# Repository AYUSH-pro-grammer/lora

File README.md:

# Lora

A LoRa board project that I made in order to figure out how radios really work, rather than just reading about them. It was a great way for me to do some PCB design and play around with KiCad, while learning what to do when things don’t go according to plan (which happened quite a bit).

# How its works

This board is a custom designed wireless communication module for long range applications. It is based on the dual-core Raspberry Pi RP2040 microcontroller and SX1262 LoRa transceiver.

- Power & Connectivity. 5V power and data thru USB-C port. An AP2112K-3.3 LDO regulator efficiently steps this down to a stable 3.3V for the system.

- Processing & Memory - The RP2040 is the brain. The RP2040 requires external memory, so it’s coupled with a W25Q16JV SPI Flash chip to store your firmware.

- Long-Range RF The SX1262 provides sub-GHz LoRa wireless communication. The RF path is controlled by a PE4259 RF switch and a Johanson Balun to condition the signal for the antenna.

- Internal Routing: The RP2040 uses its SPI busses to talk to the Flash memory and the SX1262 LoRa chip.

```text
[ USB-C ] ──5V──► [ AP2112K-3.3 LDO ] ──3.3V──┐
                                              ▼
[ W25Q16 Flash ] ◄──SPI── [ RP2040 ] ──SPI──► [ SX1262 LoRa ]
                        (Main Brain)                │
                                                    ▼
                                            [ PE4259 Switch ]
                                                    │
                                                    ▼
                                                [ Antenna ]
                                                    📡

```

# Images:

## 3d

## Schematic

## PCB 

## Components

Total Physical Components: 53
Capacitors: 28
Resistors: 8
Inductors: 3
Crystals/Oscillators: 2
Push Buttons (Cherry MX): 2
Antenna / Pin Headers: 2 (1 Spring Antenna + 1 Pin Header)
Ferrite Beads: 1
RF Baluns: 1
USB-C Connectors: 1
Voltage Regulators (AP2112K): 1
RF Switches (PE4259): 1
Flash Memory (W25Q16JV): 1
SX1262 LoRa IC: 1
RP2040 Microcontroller: 1

## BOM

|  Qty  | Component                                    | Selected Part                 | Supplier  | Link                                                                        | MOQ | Unit Price (USD) | Order Cost (USD) |
| :---: | :------------------------------------------- | :---------------------------- | :-------- | :-------------------------------------------------------------------------- | --: | ---------------: | ---------------: |
|   1   | LoRa Spring Antenna                          | BW915SNX17-5W2                | LCSC      | [Link](https://www.lcsc.com/product-detail/C496556.html)                    |   5 |           $0.165 |            $0.83 |
|   1   | Antenna Pin Header                           | 2.54-1×40P Pin Header         | LCSC      | [Link](https://www.lcsc.com/product-detail/C2337.html)                      |   5 |           $0.159 |            $0.80 |
|   12  | 100 nF Capacitor                             | 100 nF 16 V 0402 X7R          | LCSC      | [Link](https://www.lcsc.com/product-detail/C1525.html)                      | 100 |           $0.005 |            $0.46 |
|   1   | 150 pF Capacitor                             | 150 pF 50 V 0402 X7R          | LCSC      | [Link](https://www.lcsc.com/product-detail/C1527.html)                      | 100 |           $0.004 |            $0.43 |
|   1   | 20 pF Capacitor                              | 20 pF 50 V 0402 C0G           | LCSC      | [Link](https://www.lcsc.com/product-detail/C1554.html)                      | 100 |           $0.007 |            $0.69 |
|   1   | 220 pF Capacitor                             | 220 pF 50 V 0402 X7R          | LCSC      | [Link](https://www.lcsc.com/product-detail/C1530.html)                      | 100 |           $0.003 |            $0.25 |
|   1   | 1.8 pF Capacitor                             | 1.8 pF 50 V 0402 C0G          | LCSC      | [Link](https://www.lcsc.com/product-detail/C1553.html)                      | 100 |           $0.005 |            $0.50 |
|   2   | 15 pF Capacitor                              | 15 pF 50 V 0402 C0G           | LCSC      | [Link](https://www.lcsc.com/product-detail/C1548.html)                      | 100 |           $0.004 |            $0.36 |
|   2   | 12 pF Capacitor                              | 12 pF 50 V 0402 C0G           | LCSC      | [Link](https://www.lcsc.com/product-detail/C1547.html)                      | 100 |           $0.006 |            $0.60 |
|   2   | 1 pF Capacitor                               | 1 pF 50 V 0402 C0G            | LCSC      | [Link](https://www.lcsc.com/product-detail/C1550.html)                      | 100 |           $0.003 |            $0.27 |
|   3   | 160 pF Capacitor                             | 160 pF 50 V 0402 X7R          | LCSC      | [Link](https://www.lcsc.com/product-detail/C1528.html)                      | 100 |           $0.005 |            $0.51 |
|   2   | 1 µF Capacitor                               | 1 µF 16 V 0402 X5R            | LCSC      | [Link](https://www.lcsc.com/product-detail/C167339.html)                    |  50 |           $0.015 |            $0.73 |
|   1   | 1 nF Capacitor                               | 1 nF 50 V 0402 X7R            | LCSC      | [Link](https://www.lcsc.com/product-detail/C1523.html)                      | 100 |           $0.005 |            $0.51 |
|   1   | Ferrite Bead                                 | 100 Ω @ 100 MHz 0402          | LCSC      | [Link](https://www.lcsc.com/product-detail/C280601.html)                    |  20 |           $0.006 |            $0.12 |
|   1   | RF Balun                                     | 0900FM15D0039E                | LCSC      | [Link](https://www.lcsc.com/product-detail/C1513363.html)                   |   1 |           $1.214 |            $1.21 |
|   1   | USB Type-C Connector                         | TYPE-C 16PIN SMD              | LCSC      | [Link](https://www.lcsc.com/product-detail/C2765186.html)                   |  20 |           $0.071 |            $1.43 |
|   1   | 15 nH Inductor                               | 15 nH ±3% 0402                | LCSC      | [Link](https://www.lcsc.com/product-detail/C329619.html)                    |  10 |           $0.041 |            $0.41 |
|   1   | 47 nH Inductor                               | 47 nH ±2% 0402                | LCSC      | [Link](https://www.lcsc.com/product-detail/C22334.html)                     |  10 |           $0.064 |            $0.64 |
|   1   | 9.1 nH Inductor                              | 9.1 nH ±2% 0402               | LCSC      | [Link](https://www.lcsc.com/product-detail/C7516935.html)                   |   1 |           $0.095 |            $0.09 |
|   1   | 100 Ω Resistor                               | 100 Ω ±1% 0402                | LCSC      | [Link](https://www.lcsc.com/product-detail/C25076.html)                     | 100 |           $0.004 |            $0.37 |
|   2   | 10 kΩ Resistor                               | 10 kΩ ±1% 0402                | LCSC      | [Link](https://www.lcsc.com/product-detail/C25744.html)                     | 100 |           $0.003 |            $0.31 |
|   1   | 150 Ω Resistor                               | 150 Ω ±1% 0402                | LCSC      | [Link](https://www.lcsc.com/product-detail/C25082.html)                     | 100 |           $0.002 |            $0.19 |
|   1   | 140 Ω Resistor                               | 140 Ω ±1% 0402                | LCSC      | [Link](https://www.lcsc.com/product-detail/C25081.html)                     | 100 |           $0.002 |            $0.20 |
|   2   | 5.1 kΩ Resistor                              | 5.1 kΩ ±1% 0402               | LCSC      | [Link](https://www.lcsc.com/product-detail/C25905.html)                     | 100 |           $0.002 |            $0.23 |
|   1   | 2.2 kΩ Resistor                              | 2.2 kΩ ±1% 0402               | LCSC      | [Link](https://www.lcsc.com/product-detail/C25879.html)                     | 100 |           $0.004 |            $0.35 |
|   1   | Microcontroller                              | RP2040 (QFN-56)               | LCSC      | [Link](https://www.lcsc.com/product-detail/C2040.html)                      |   1 |           $0.997 |            $1.00 |
|   1   | LoRa Transceiver                             | SX1262IMLTRT (QFN-24)         | LCSC      | [Link](https://www.lcsc.com/product-detail/C191341.html)                    |   1 |           $3.222 |            $3.22 |
|   1   | RF Switch / LDO                              | LM337BTG                      | LCSC      | [Link](https://www.lcsc.com/product-detail/C74415.html)                     |   1 |           $0.673 |            $0.67 |
|   1   | 3.3 V LDO Regulator                          | AP2112K-3.3TRG1               | LCSC      | [Link](https://www.lcsc.com/product-detail/C51118.html)                     |   5 |           $0.173 |            $0.86 |
|   1   | SPI Flash Memory                             | W25Q16JVSSIQ (SOIC-8)         | LCSC      | [Link](https://www.lcsc.com/product-detail/C82317.html)                     |   1 |           $1.023 |            $1.02 |
|   1   | 32 MHz Crystal                               | X322532MMB4SI                 | LCSC      | [Link](https://www.lcsc.com/product-detail/C113671.html)                    |   5 |           $0.108 |            $0.54 |
|   1   | 12 MHz Crystal                               | X322512MSB4SI                 | LCSC      | [Link](https://www.lcsc.com/product-detail/C9002.html)                      |   5 |           $0.096 |            $0.48 |
|   2   | Tactile Switch                               | Cherry MX Clear (Pack of 10)  | StacksKB  | [Link](https://stackskb.com/store/cherry-mx-clear-switch-5-pin-pack-of-10/) |  10 |           $0.480 |            $4.80 |
|   1   | OLED Display                                 | 0.96 Inch OLED Display Module | RoboCraze | [Link](https://robocraze.com/products/0-96in-oled-display-module-4pin)      |   1 |            $1.74 |            $1.74 |
| **—** | **Total Procurement Cost (1st Batch Order)** |                               |           |                                                                             |     |                  |      **~$26.82** |

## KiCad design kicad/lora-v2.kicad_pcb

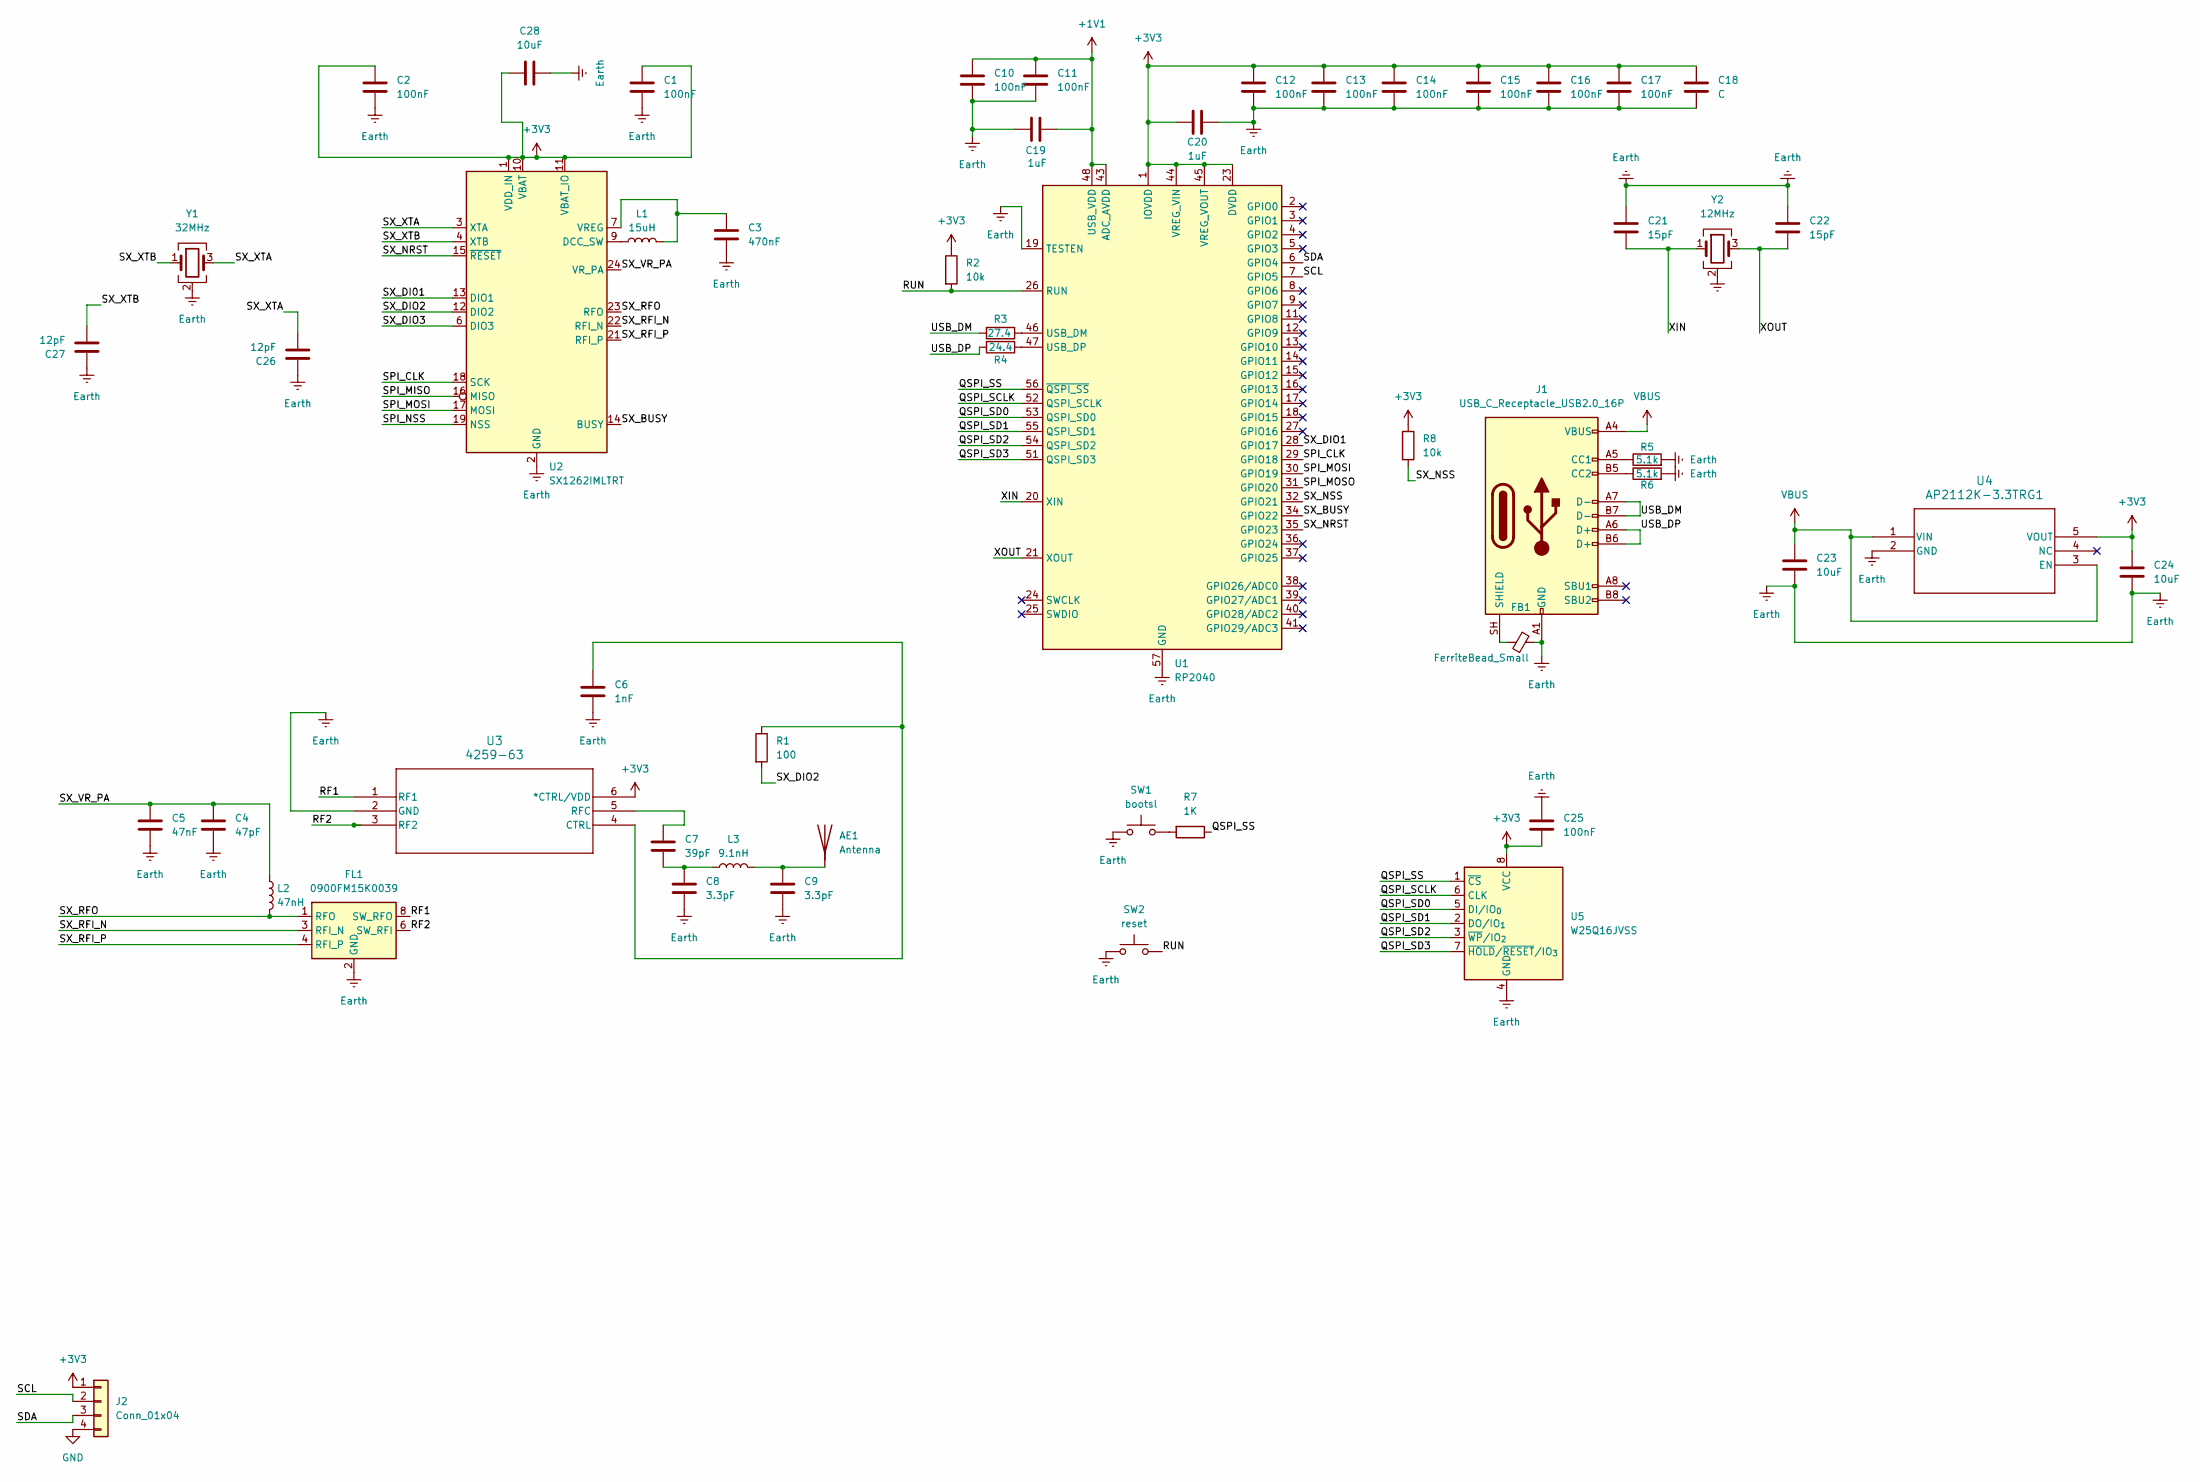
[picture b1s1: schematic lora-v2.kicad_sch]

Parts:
AE1: Antenna; PinSocket_1x01_P2.54mm_Vertical
C1, C2, C10, C11, C12, C13, C14, C15, C16, C17, C25: 100nF; C_0402_1005Metric
C3: 470nF; C_0402_1005Metric
C4: 47pF; C_0402_1005Metric
C5: 47nF; C_0402_1005Metric
C6: 1nF; C_0402_1005Metric
C7: 39pF; C_0402_1005Metric
C8, C9: 3.3pF; C_0402_1005Metric
C18: C; C_0402_1005Metric
C19, C20: 1uF; C_0402_1005Metric
C21, C22: 15pF; C_0402_1005Metric
C23, C24, C28: 10uF; C_0402_1005Metric
C26, C27: 12pF; C_0402_1005Metric
FB1: FerriteBead_Small; L_0402_1005Metric
FL1: 0900FM15K0039; Balun_Johanson_0900FM15K0039
J1: USB_C_Receptacle_USB2.0_16P; USB_C_Receptacle_GCT_USB4105-xx-A_16P_TopMnt_Horizontal
J2: Conn_01x04; PinHeader_1x04_P2.54mm_Vertical
L1: 15uH; L_0402_1005Metric
L2: 47nH; L_0402_1005Metric
L3: 9.1nH; L_0402_1005Metric
R1: 100; R_0402_1005Metric
R2, R8: 10k; R_0402_1005Metric
R3: 27.4; R_0402_1005Metric
R4: 24.4; R_0402_1005Metric
R5, R6: 5.1k; R_0402_1005Metric
R7: 1K; R_0402_1005Metric
SW1: bootsl; SW_Tactile_SPST_NO_Straight_CK_PTS636Sx25SMTRLFS
SW2: reset; SW_Tactile_SPST_NO_Straight_CK_PTS636Sx25SMTRLFS
U1: RP2040; QFN-56-1EP_7x7mm_P0.4mm_EP3.2x3.2mm
U2: SX1262IMLTRT; QFN-24-1EP_4x4mm_P0.5mm_EP2.6x2.6mm
U3: 4259-63; SOT-363_SC-70-6
U4: AP2112K-3.3TRG1; SOT-23-5
U5: W25Q16JVSS; SOIC-8_5.3x5.3mm_P1.27mm
Y1: 32MHz; Crystal_SMD_3225-4Pin_3.2x2.5mm
Y2: 12MHz; Crystal_SMD_Abracon_ABM8G-4Pin_3.2x2.5mm

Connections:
+1V1: C10.1, C11.1, C19.2, U1.43 (ADC_AVDD), U1.48 (USB_VDD)
+3V3: C1.1, C2.1, C12.1, C13.1, C14.1, C15.1, C16.1, C17.1, C18.1, C20.2, C24.1, C25.2, C28.1, J2.1, R2.1, R8.1, U1.1 (IOVDD), U1.10 (IOVDD), U1.22 (IOVDD), U1.23 (DVDD), U1.33 (IOVDD), U1.42 (IOVDD), U1.44 (VREG_VIN), U1.45 (VREG_VOUT), U1.49 (IOVDD), U1.50 (DVDD), U2.1 (VDD_IN), U2.10 (VBAT), U2.11 (VBAT_IO), U3.6 (*CTRL/VDD), U4.5 (VOUT), U5.8 (VCC)
/QSPI_SCLK: U1.52 (QSPI_SCLK), U5.6 (CLK)
/QSPI_SD0: U1.53 (QSPI_SD0), U5.5 (DI/IO_{0})
/QSPI_SD1: U1.55 (QSPI_SD1), U5.2 (DO/IO_{1})
/QSPI_SD2: U1.54 (QSPI_SD2), U5.3 (~WP/IO_{2})
/QSPI_SD3: U1.51 (QSPI_SD3), U5.7 (~HOLD/~RESET/IO_{3})
/QSPI_SS: R7.1, U1.56 (~QSPI_SS), U5.1 (~CS)
/RF1: FL1.8 (SW_RFO), U3.1 (RF1)
/RF2: FL1.6 (SW_RFI), U3.3 (RF2)
/RUN: R2.2, SW2.2, U1.26 (RUN)
/SCL: J2.2, U1.7 (GPIO5)
/SDA: J2.3, U1.6 (GPIO4)
/SPI_CLK: U1.29 (GPIO18), U2.18 (SCK)
/SPI_MISO: U2.16 (MISO)
/SPI_MOSI: U1.30 (GPIO19), U2.17 (MOSI)
/SPI_MOSO: U1.31 (GPIO20)
/SPI_NSS: U2.19 (NSS)
/SX_BUSY: U1.34 (GPIO22), U2.14 (BUSY)
/SX_DI01: U2.13 (DIO1)
/SX_DIO1: U1.28 (GPIO17)
/SX_DIO2: R1.2, U2.12 (DIO2)
/SX_DIO3: U2.6 (DIO3)
/SX_NRST: U1.35 (GPIO23), U2.15 (~RESET)
/SX_NSS: R8.2, U1.32 (GPIO21)
/SX_RFI_N: FL1.3 (RFI_N), U2.22 (RFI_N)
/SX_RFI_P: FL1.4 (RFI_P), U2.21 (RFI_P)
/SX_RFO: FL1.1 (RFO), L2.2, U2.23 (RFO)
/SX_VR_PA: C4.1, C5.1, L2.1, U2.24 (VR_PA)
/SX_XTA: C26.2, U2.3 (XTA), Y1.3
/SX_XTB: C27.2, U2.4 (XTB), Y1.1
/USB_DM: J1.A7 (D-), J1.B7 (D-), R3.2
/USB_DP: J1.A6 (D+), J1.B6 (D+), R4.2
/XIN: C21.2, U1.20 (XIN), Y2.1
/XOUT: C22.2, U1.21 (XOUT), Y2.3
Earth: C1.2, C2.2, C3.2, C4.2, C5.2, C6.2, C8.2, C9.2, C10.2, C11.2, C12.2, C13.2, C14.2, C15.2, C16.2, C17.2, C18.2, C19.1, C20.1, C21.1, C22.1, C23.2, C24.2, C25.1, C26.1, C27.1, C28.2, FB1.1, FL1.2 (GND), FL1.5 (GND), FL1.7 (GND), FL1.9 (GND), FL1.10 (GND), J1.A1 (GND), J1.A12 (GND), J1.B1 (GND), J1.B12 (GND), R5.2, R6.2, SW1.1, SW2.1, U1.19 (TESTEN), U1.57 (GND), U2.2 (GND), U2.5 (GND), U2.8 (GND), U2.20 (GND), U2.25 (GND), U3.2 (GND), U4.2 (GND), U5.4 (GND), Y1.2 (G), Y1.4 (G), Y2.2 (G), Y2.4 (G)
GND: J2.4
unnamed: AE1.1 (A_1), C9.1, L3.2
unnamed: C7.2, C8.1, L3.1
unnamed: J1.A5 (CC1), R5.1
unnamed: J1.B5 (CC2), R6.1
unnamed: FB1.2, J1.SH (SHIELD)
unnamed: R7.2, SW1.2
unnamed: R3.1, U1.46 (USB_DM)
unnamed: R4.1, U1.47 (USB_DP)
unnamed: L1.1, U2.9 (DCC_SW)
unnamed: C3.1, L1.2, U2.7 (VREG)
unnamed: C6.1, R1.1, U3.4 (CTRL)
unnamed: C7.1, U3.5 (RFC)
VBUS: C23.1, J1.A4 (VBUS), J1.A9 (VBUS), J1.B4 (VBUS), J1.B9 (VBUS), U4.1 (VIN), U4.3 (EN)

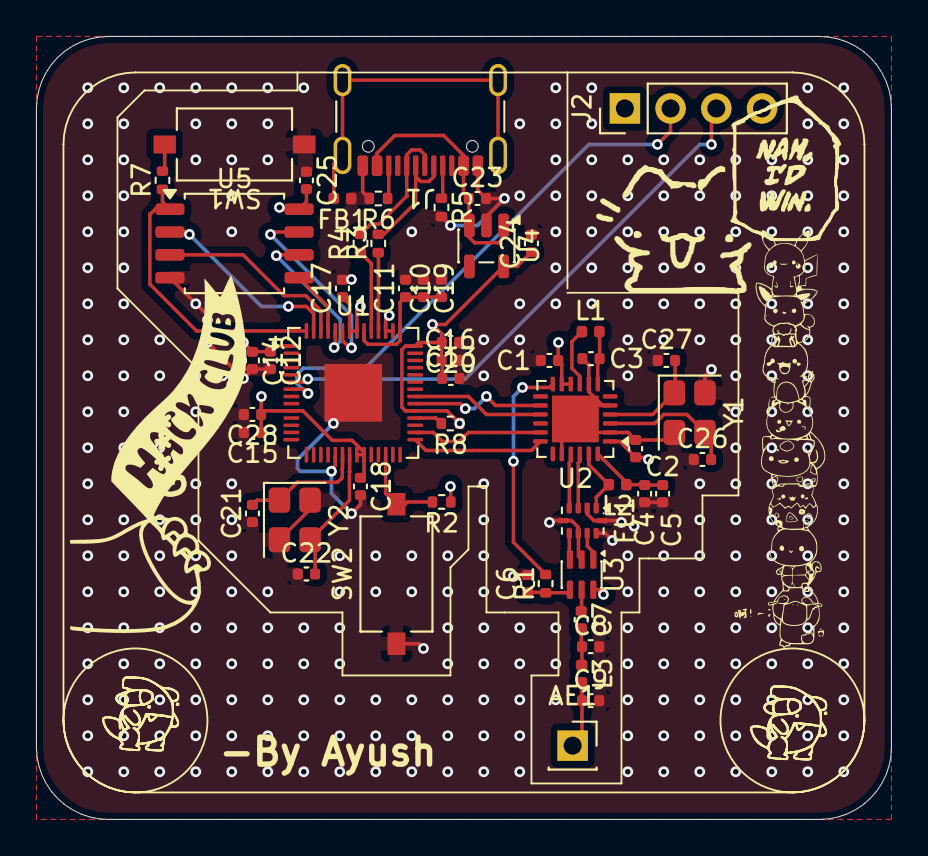
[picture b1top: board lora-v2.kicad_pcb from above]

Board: 4 copper layers, 47.5 x 43.5 mm, 53 parts (0 on the bottom side), 43 nets.
